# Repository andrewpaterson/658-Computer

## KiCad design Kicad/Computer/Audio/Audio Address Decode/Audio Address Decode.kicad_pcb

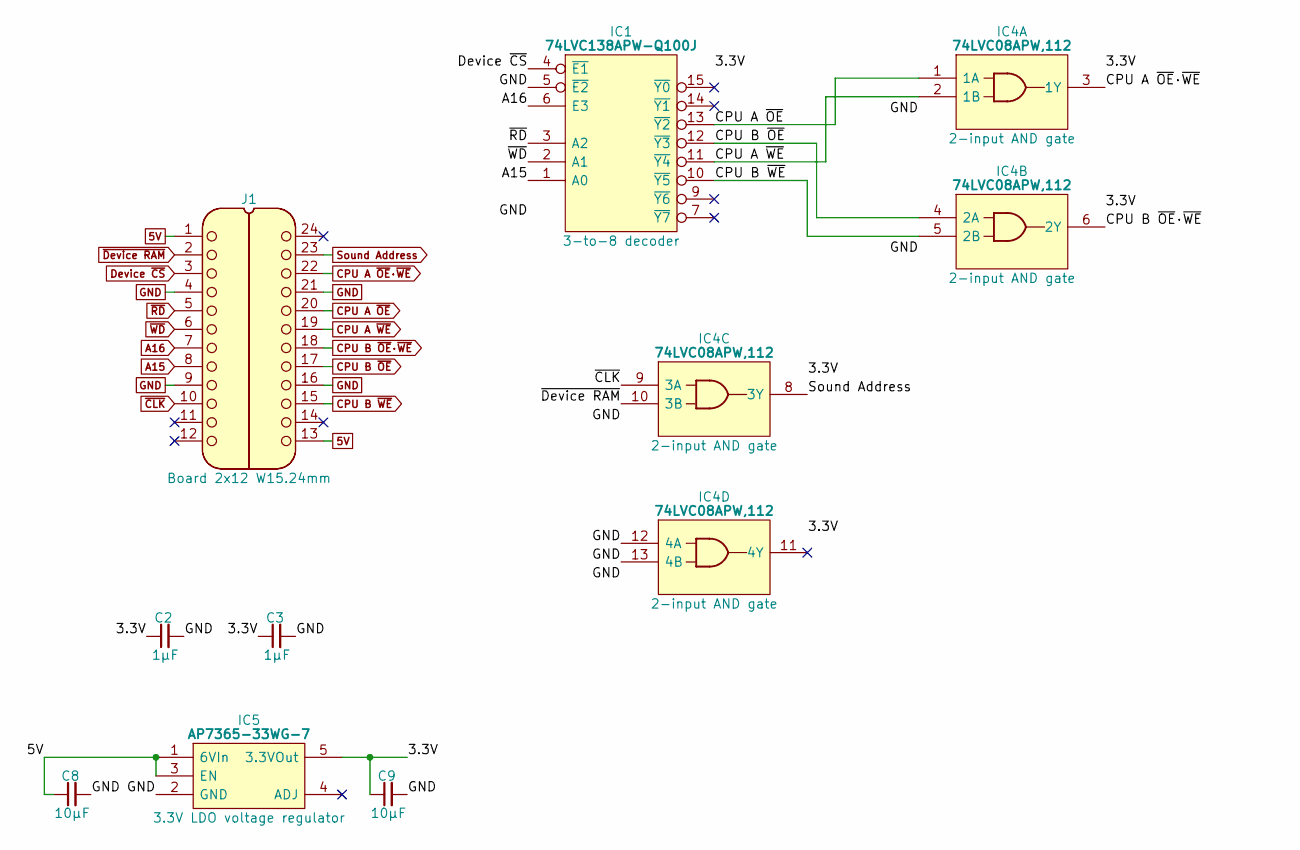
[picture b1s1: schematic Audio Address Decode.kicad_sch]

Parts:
C2, C3: 1μF; C_0805
C8, C9: 10µF; C_0805
IC1: 74LVC138APW-Q100J; SOP65P640X110-16N; Mouser Part Number 771-74LVC138APWQ100J
IC4: 74LVC08APW,112; SOP65P640X110-14N; Manufacturer_Part_Number 74LVC08APW,112; Mouser Part Number 771-74LVC08APW
IC5: AP7365-33WG-7; SOT95P285X130-5N; Manufacturer_Part_Number AP7365-33WG-7; Mouser Part Number 621-AP7365-33WG-7
J1: Board 2x12 W15.24mm; DIP-24_Board_W15.24mm

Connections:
5V: C8.1, IC5.1 (6VIn), IC5.3 (EN), J1.1, J1.13
/3.3V: C2.1, C3.1, C9.1, IC1.16 (3V), IC4.14 (3V), IC5.5 (3.3VOut)
A15: IC1.1 (A0), J1.8
A16: IC1.6 (E3), J1.7
CPU A ~OE: IC1.13 (~Y2), IC4.1 (1A), J1.20
CPU A ~OE·~WE: IC4.3 (1Y), J1.22
CPU A ~WE: IC1.11 (~Y4), IC4.2 (1B), J1.19
CPU B ~OE: IC1.12 (~Y3), IC4.4 (2A), J1.17
CPU B ~OE·~WE: IC4.6 (2Y), J1.18
CPU B ~WE: IC1.10 (~Y5), IC4.5 (2B), J1.15
Device ~CS: IC1.4 (~E1), J1.3
GND: C2.2, C3.2, C8.2, C9.2, IC1.5 (~E2), IC1.8 (GND), IC4.7 (GND), IC4.12 (4A), IC4.13 (4B), IC5.2 (GND), J1.4, J1.9, J1.16, J1.21
Sound Address: IC4.8 (3Y), J1.23
~CLK: IC4.9 (3A), J1.10
~Device RAM: IC4.10 (3B), J1.2
~RD: IC1.3 (A2), J1.5
~WD: IC1.2 (A1), J1.6

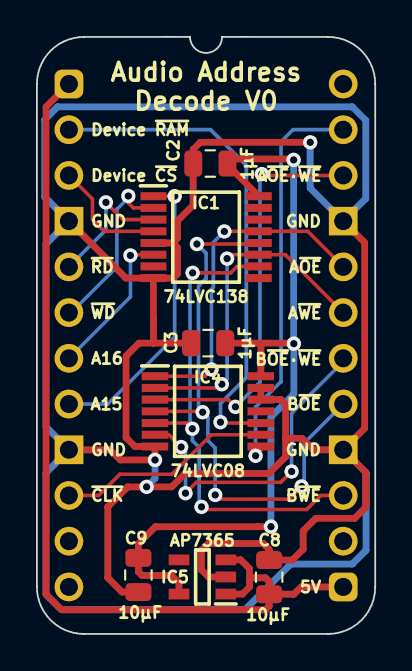
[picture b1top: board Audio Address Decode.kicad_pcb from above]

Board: 2 copper layers, 18.8 x 33.2 mm, 8 parts (0 on the bottom side), 17 nets.

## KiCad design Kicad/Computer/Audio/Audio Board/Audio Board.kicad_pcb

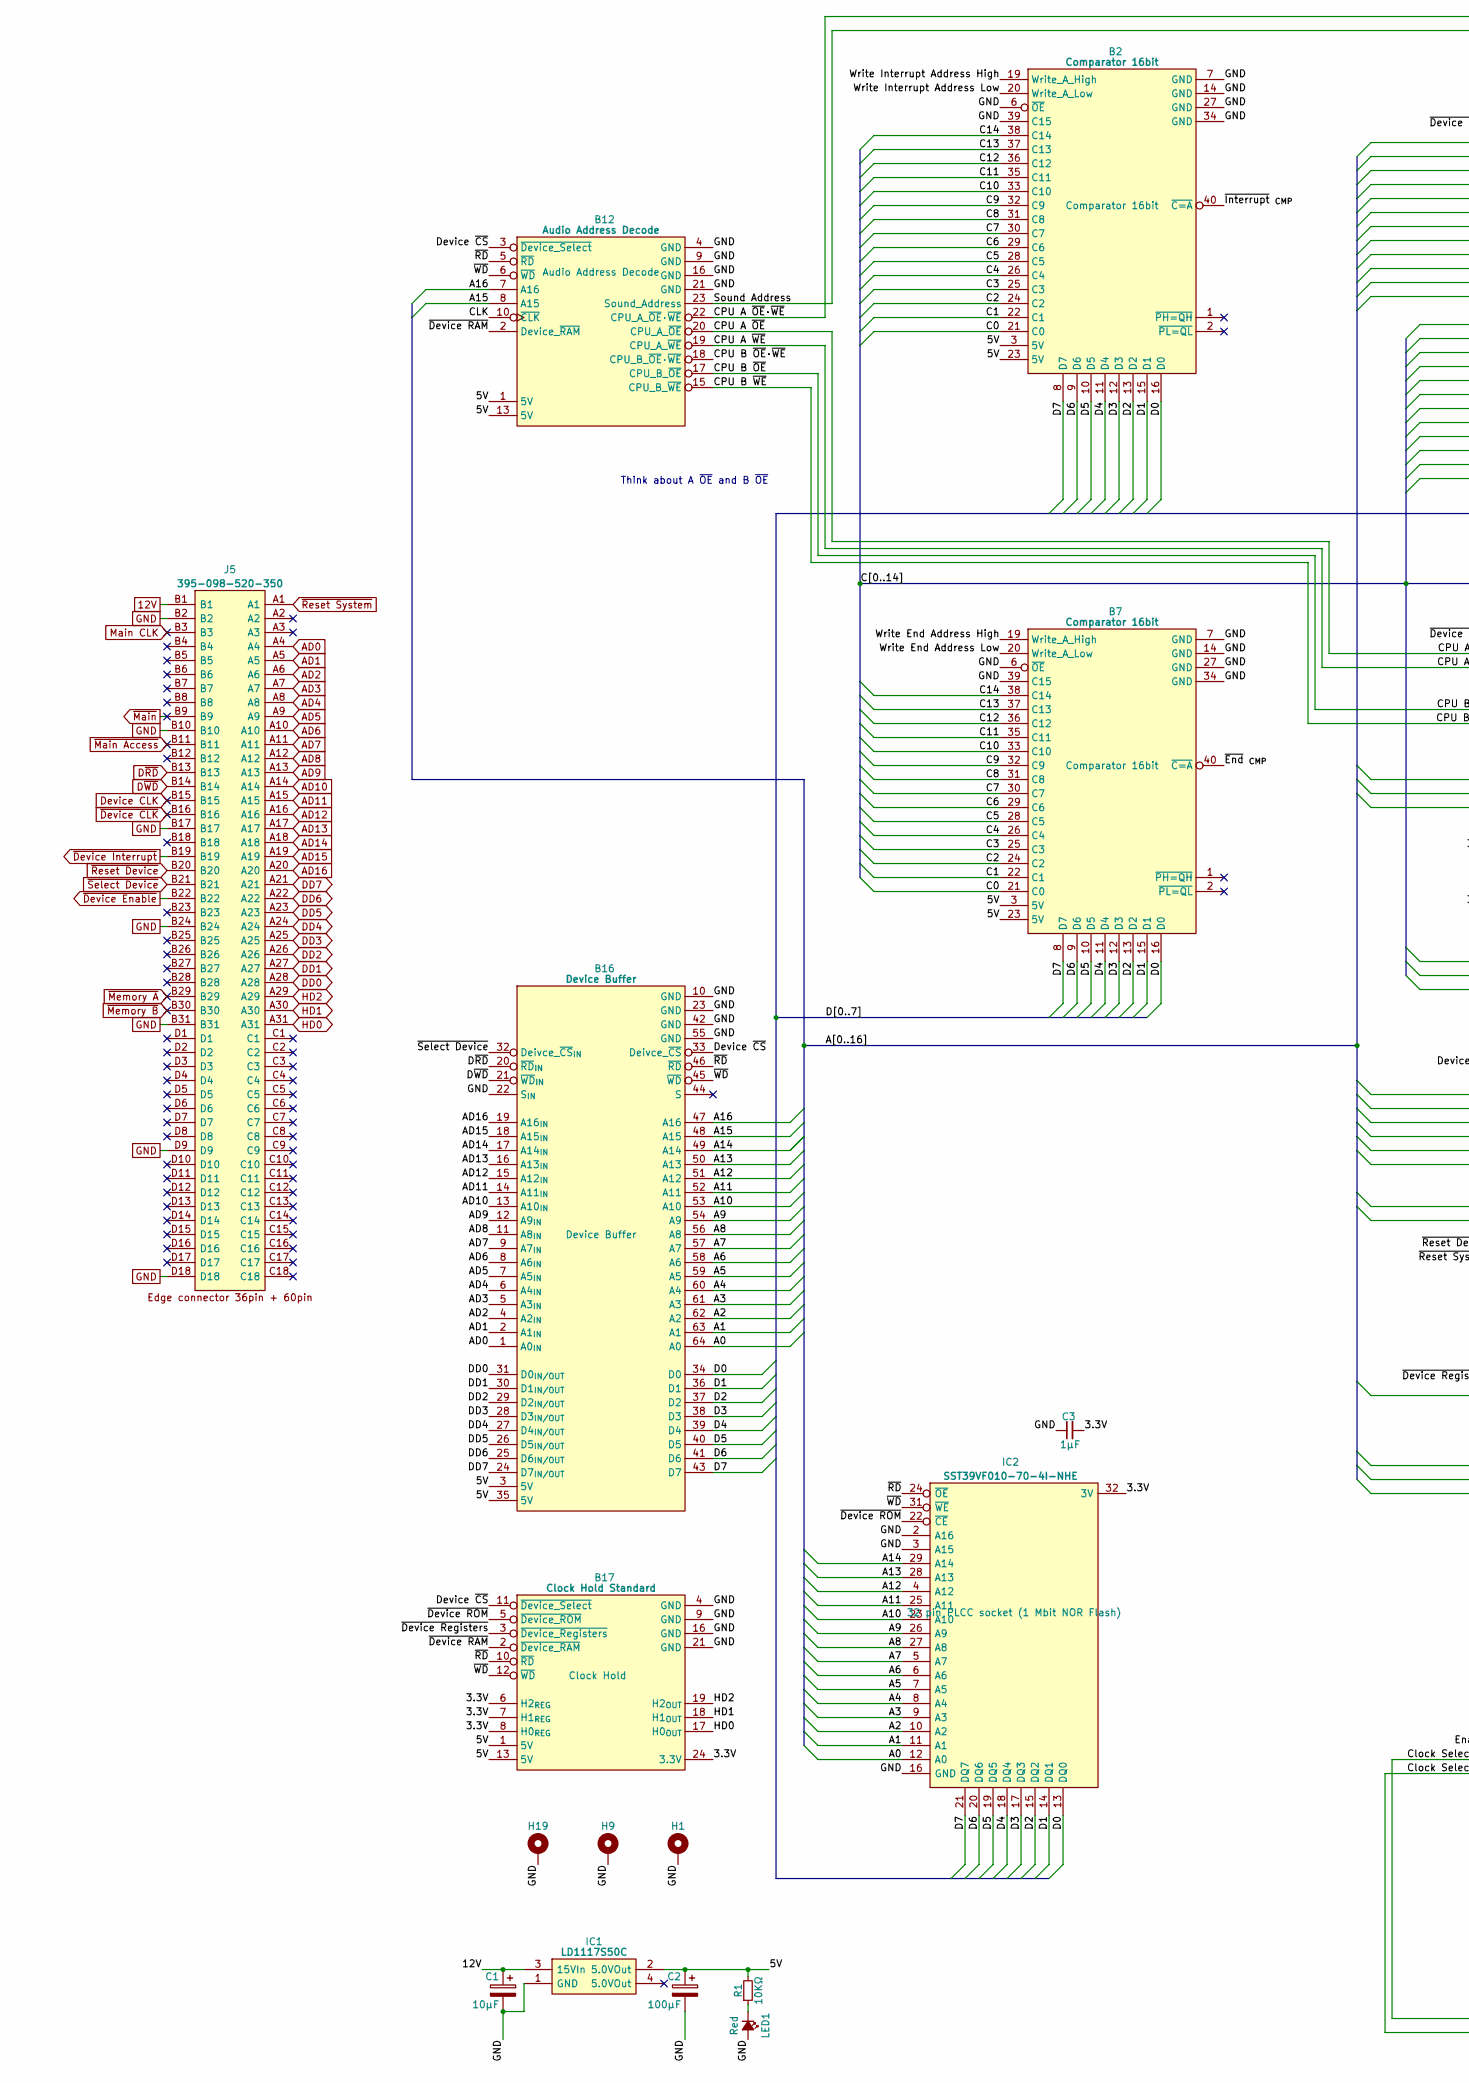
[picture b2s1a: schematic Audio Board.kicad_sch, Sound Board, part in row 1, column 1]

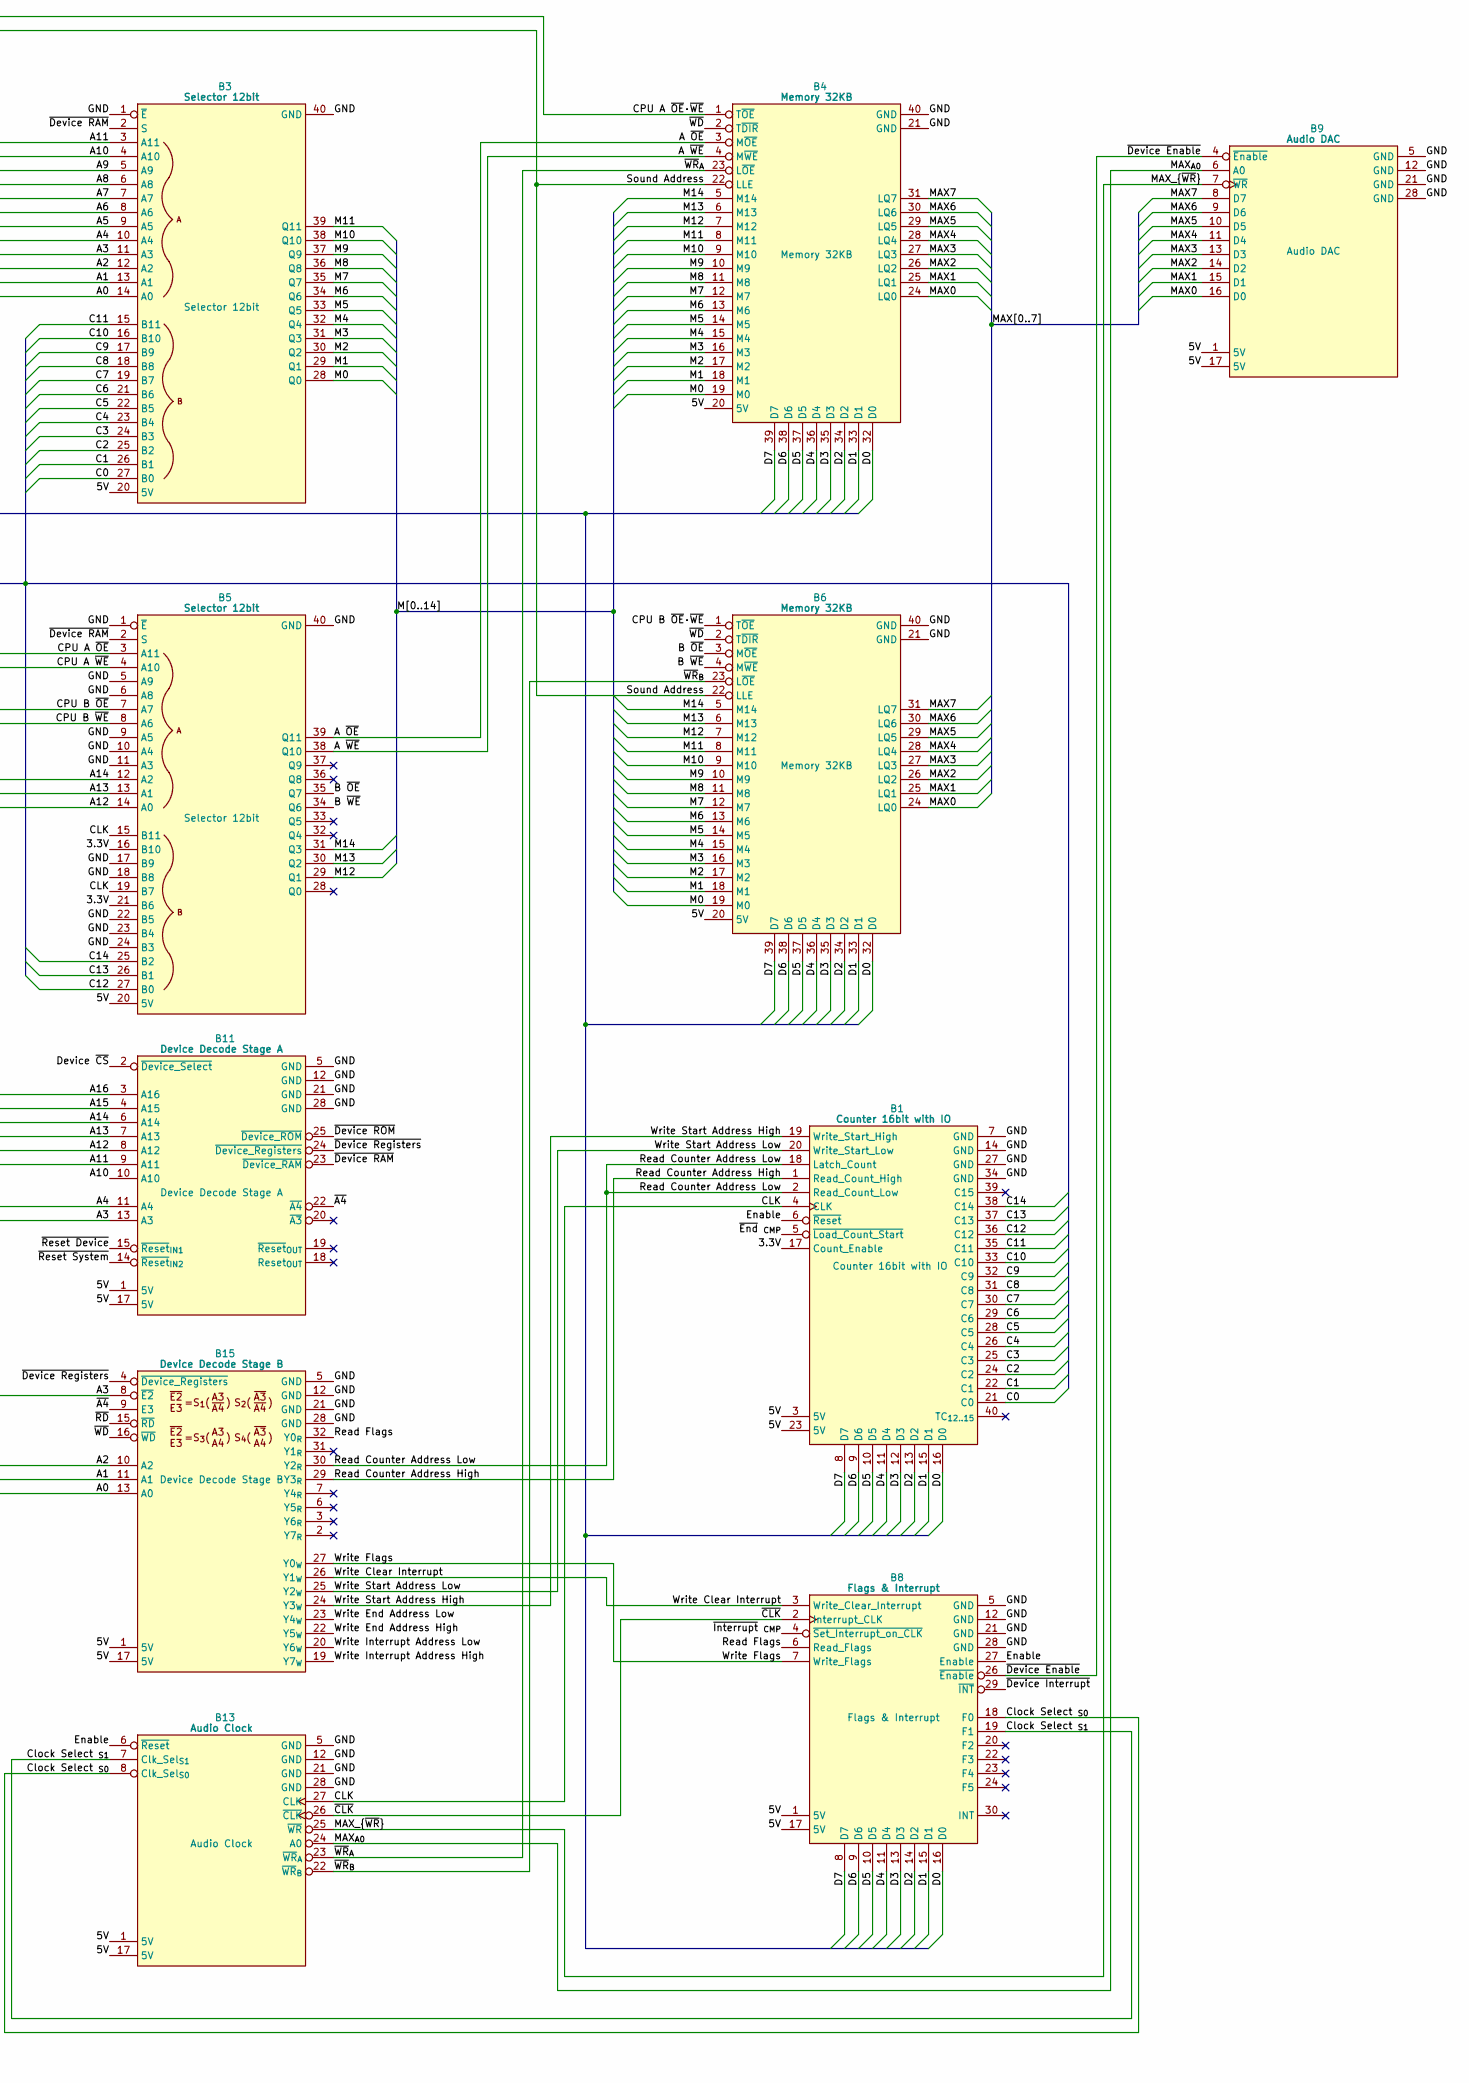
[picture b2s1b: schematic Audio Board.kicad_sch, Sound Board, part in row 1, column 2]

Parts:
B1: Counter 16bit with IO; HCP65_Counter_16bit_DIO
B2, B7: Comparator 16bit; HCP65_Comparator_16bit
B3, B5: Selector 12bit; HCP65_Selector_12bit
B4, B6: Memory 32KB; HCP65_Memory_32KB_With_Latch
B8: Flags & Interrupt; HCP65_Flags_Interrupt
B9: Audio DAC; HCP65_Audio_DAC
B11: Device Decode Stage A; HCP65_Device_Decode_Stage_A
B12: Audio Address Decode; HCP65_Audio_Address_Decode
B13: Audio Clock; HCP65_Audio_Clock
B15: Device Decode Stage B; HCP65_Device_Decode_Stage_B
B16: Device Buffer; HCP65_Device_Buffer
B17: Clock Hold Standard; HCP65_Clock_Hold_Standard
C1: 10μF; CP_Radial_D4.0mm_P2.00mm
C2: 100μF; CP_Radial_D4.0mm_P2.00mm
C3: 1μF; C_0805
H1, H9, H19: MountingHole_Pad; HCP65_MountingHole_M3_
IC1: LD1117S50C; LD1117S33C; Manufacturer_Part_Number LD1117S50C
IC2: SST39VF010-70-4I-NHE; 5408803224008; Manufacturer_Part_Number SST39VF010-70-4I-NHE
J5: 395-098-520-350; 98pin Edge Connector; Manufacturer_Part_Number 395-098-520-350; Mouser Part Number 587-395-098-520-350
LED1: Red; LED_D5.0mm
R1: 10KΩ; R_0805

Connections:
12V: C1.1, IC1.3 (15VIn), J5.B1
/3.3V: B1.17 (Count_Enable), B5.16 (B10), B5.21 (B6), B17.6 (H2_{REG}), B17.7 (H1_{REG}), B17.8 (H0_{REG}), B17.24 (3.3V), C3.2, IC2.32 (3V)
/5V: B1.3 (5V), B1.23 (5V), B2.3 (5V), B2.23 (5V), B3.20 (5V), B4.20 (5V), B5.20 (5V), B6.20 (5V), B7.3 (5V), B7.23 (5V), B8.1 (5V), B8.17 (5V), B9.1 (5V), B9.17 (5V), B11.1 (5V), B11.17 (5V), B12.1 (5V), B12.13 (5V), B13.1 (5V), B13.17 (5V), B15.1 (5V), B15.17 (5V), B16.3 (5V), B16.35 (5V), B17.1 (5V), B17.13 (5V), C2.1, IC1.2 (5.0VOut), R1.2
/A0: B3.14 (A0), B15.13 (A0), B16.64 (A0), IC2.12 (A0)
/A1: B3.13 (A1), B15.11 (A1), B16.63 (A1), IC2.11 (A1)
/A2: B3.12 (A2), B15.10 (A2), B16.62 (A2), IC2.10 (A2)
/A3: B3.11 (A3), B11.13 (A3), B15.8 (~E2), B16.61 (A3), IC2.9 (A3)
/A4: B3.10 (A4), B11.11 (A4), B16.60 (A4), IC2.8 (A4)
/A5: B3.9 (A5), B16.59 (A5), IC2.7 (A5)
/A6: B3.8 (A6), B16.58 (A6), IC2.6 (A6)
/A7: B3.7 (A7), B16.57 (A7), IC2.5 (A7)
/A8: B3.6 (A8), B16.56 (A8), IC2.27 (A8)
/A9: B3.5 (A9), B16.54 (A9), IC2.26 (A9)
/A10: B3.4 (A10), B11.10 (A10), B16.53 (A10), IC2.23 (A10)
/A11: B3.3 (A11), B11.9 (A11), B16.52 (A11), IC2.25 (A11)
/A12: B5.14 (A0), B11.8 (A12), B16.51 (A12), IC2.4 (A12)
/A13: B5.13 (A1), B11.7 (A13), B16.50 (A13), IC2.28 (A13)
/A14: B5.12 (A2), B11.6 (A14), B16.49 (A14), IC2.29 (A14)
/A15: B11.4 (A15), B12.8 (A15), B16.48 (A15)
/A16: B11.3 (A16), B12.7 (A16), B16.47 (A16)
/A ~OE: B4.3 (M~OE), B5.39 (Q11)
/A ~WE: B4.4 (M~WE), B5.38 (Q10)
/B ~OE: B5.35 (Q7), B6.3 (M~OE)
/B ~WE: B5.34 (Q6), B6.4 (M~WE)
/C0: B1.21 (C0), B2.21 (C0), B3.27 (B0), B7.21 (C0)
/C1: B1.22 (C1), B2.22 (C1), B3.26 (B1), B7.22 (C1)
/C2: B1.24 (C2), B2.24 (C2), B3.25 (B2), B7.24 (C2)
/C3: B1.25 (C3), B2.25 (C3), B3.24 (B3), B7.25 (C3)
/C4: B1.26 (C4), B2.26 (C4), B3.23 (B4), B7.26 (C4)
/C5: B1.28 (C5), B2.28 (C5), B3.22 (B5), B7.28 (C5)
/C6: B1.29 (C6), B2.29 (C6), B3.21 (B6), B7.29 (C6)
/C7: B1.30 (C7), B2.30 (C7), B3.19 (B7), B7.30 (C7)
/C8: B1.31 (C8), B2.31 (C8), B3.18 (B8), B7.31 (C8)
/C9: B1.32 (C9), B2.32 (C9), B3.17 (B9), B7.32 (C9)
/C10: B1.33 (C10), B2.33 (C10), B3.16 (B10), B7.33 (C10)
/C11: B1.35 (C11), B2.35 (C11), B3.15 (B11), B7.35 (C11)
/C12: B1.36 (C12), B2.36 (C12), B5.27 (B0), B7.36 (C12)
/C13: B1.37 (C13), B2.37 (C13), B5.26 (B1), B7.37 (C13)
/C14: B1.38 (C14), B2.38 (C14), B5.25 (B2), B7.38 (C14)
/CLK: B1.4 (CLK), B5.15 (B11), B5.19 (B7), B12.10 (~CLK), B13.27 (CLK)
/CPU A ~OE: B5.3 (A11), B12.20 (CPU_A_~OE)
/CPU A ~OE·~WE: B4.1 (T~OE), B12.22 (CPU_A_~OE·~WE)
/CPU A ~WE: B5.4 (A10), B12.19 (CPU_A_~WE)
/CPU B ~OE: B5.7 (A7), B12.17 (CPU_B_~OE)
/CPU B ~OE·~WE: B6.1 (T~OE), B12.18 (CPU_B_~OE·~WE)
/CPU B ~WE: B5.8 (A6), B12.15 (CPU_B_~WE)
/Clock Select _{S0}: B8.18 (F0), B13.8 (Clk_Sel_{S0})
/Clock Select _{S1}: B8.19 (F1), B13.7 (Clk_Sel_{S1})
/D0: B1.16 (D0), B2.16 (D0), B4.32 (D0), B6.32 (D0), B7.16 (D0), B8.16 (D0), B16.34 (D0), IC2.13 (DQ0)
/D1: B1.15 (D1), B2.15 (D1), B4.33 (D1), B6.33 (D1), B7.15 (D1), B8.15 (D1), B16.36 (D1), IC2.14 (DQ1)
/D2: B1.13 (D2), B2.13 (D2), B4.34 (D2), B6.34 (D2), B7.13 (D2), B8.14 (D2), B16.37 (D2), IC2.15 (DQ2)
/D3: B1.12 (D3), B2.12 (D3), B4.35 (D3), B6.35 (D3), B7.12 (D3), B8.13 (D3), B16.38 (D3), IC2.17 (DQ3)
/D4: B1.11 (D4), B2.11 (D4), B4.36 (D4), B6.36 (D4), B7.11 (D4), B8.11 (D4), B16.39 (D4), IC2.18 (DQ4)
/D5: B1.10 (D5), B2.10 (D5), B4.37 (D5), B6.37 (D5), B7.10 (D5), B8.10 (D5), B16.40 (D5), IC2.19 (DQ5)
/D6: B1.9 (D6), B2.9 (D6), B4.38 (D6), B6.38 (D6), B7.9 (D6), B8.9 (D6), B16.41 (D6), IC2.20 (DQ6)
/D7: B1.8 (D7), B2.8 (D7), B4.39 (D7), B6.39 (D7), B7.8 (D7), B8.8 (D7), B16.43 (D7), IC2.21 (DQ7)
/Device ~CS: B11.2 (~Device_Select), B12.3 (~Device_Select), B16.33 (Deivce_~CS), B17.11 (~Device_Select)
/Enable: B1.6 (~Reset), B8.27 (Enable), B13.6 (~Reset)
/M0: B3.28 (Q0), B4.19 (M0), B6.19 (M0)
/M1: B3.29 (Q1), B4.18 (M1), B6.18 (M1)
/M2: B3.30 (Q2), B4.17 (M2), B6.17 (M2)
/M3: B3.31 (Q3), B4.16 (M3), B6.16 (M3)
/M4: B3.32 (Q4), B4.15 (M4), B6.15 (M4)
/M5: B3.33 (Q5), B4.14 (M5), B6.14 (M5)
/M6: B3.34 (Q6), B4.13 (M6), B6.13 (M6)
/M7: B3.35 (Q7), B4.12 (M7), B6.12 (M7)
/M8: B3.36 (Q8), B4.11 (M8), B6.11 (M8)
/M9: B3.37 (Q9), B4.10 (M9), B6.10 (M9)
/M10: B3.38 (Q10), B4.9 (M10), B6.9 (M10)
/M11: B3.39 (Q11), B4.8 (M11), B6.8 (M11)
/M12: B4.7 (M12), B5.29 (Q1), B6.7 (M12)
/M13: B4.6 (M13), B5.30 (Q2), B6.6 (M13)
/M14: B4.5 (M14), B5.31 (Q3), B6.5 (M14)
/MAX0: B4.24 (LQ0), B6.24 (LQ0), B9.16 (D0)
/MAX1: B4.25 (LQ1), B6.25 (LQ1), B9.15 (D1)
/MAX2: B4.26 (LQ2), B6.26 (LQ2), B9.14 (D2)
/MAX3: B4.27 (LQ3), B6.27 (LQ3), B9.13 (D3)
/MAX4: B4.28 (LQ4), B6.28 (LQ4), B9.11 (D4)
/MAX5: B4.29 (LQ5), B6.29 (LQ5), B9.10 (D5)
/MAX6: B4.30 (LQ6), B6.30 (LQ6), B9.9 (D6)
/MAX7: B4.31 (LQ7), B6.31 (LQ7), B9.8 (D7)
/MAX_{A0}: B9.6 (A0), B13.24 (A0)
/MAX_{~WR}: B9.7 (~WR), B13.25 (~WR)
/Read Counter Address High: B1.1 (Read_Count_High), B15.29 (Y3_{R})
/Read Counter Address Low: B1.2 (Read_Count_Low), B1.18 (Latch_Count), B15.30 (Y2_{R})
/Read Flags: B8.6 (Read_Flags), B15.32 (Y0_{R})
/Sound Address: B4.22 (LLE), B6.22 (LLE), B12.23 (Sound_Address)
/Write Clear Interrupt: B8.3 (Write_Clear_Interrupt), B15.26 (Y1_{W})
/Write End Address High: B7.19 (Write_A_High), B15.22 (Y5_{W})
/Write End Address Low: B7.20 (Write_A_Low), B15.23 (Y4_{W})
/Write Flags: B8.7 (Write_Flags), B15.27 (Y0_{W})
/Write Interrupt Address High: B2.19 (Write_A_High), B15.19 (Y7_{W})
/Write Interrupt Address Low: B2.20 (Write_A_Low), B15.20 (Y6_{W})
/Write Start Address High: B1.19 (Write_Start_High), B15.24 (Y3_{W})
/Write Start Address Low: B1.20 (Write_Start_Low), B15.25 (Y2_{W})
/~A4: B11.22 (~A4), B15.9 (E3)
/~CLK: B8.2 (Interrupt_CLK), B13.26 (~CLK)
/~Device RAM: B3.2 (S), B5.2 (S), B11.23 (~Device_RAM), B12.2 (Device_~RAM), B17.2 (~Device_RAM)
/~Device ROM: B11.25 (~Device_ROM), B17.5 (~Device_ROM), IC2.22 (~CE)
/~Device Registers: B11.24 (~Device_Registers), B15.4 (~Device_Registers), B17.3 (~Device_Registers)
/~End _{CMP}: B1.5 (~Load_Count_Start), B7.40 (~C=A)
/~Interrupt _{CMP}: B2.40 (~C=A), B8.4 (~Set_Interrupt_on_CLK)
/~RD: B12.5 (~RD), B15.15 (~RD), B16.46 (~RD), B17.10 (~RD), IC2.24 (~OE)
/~WD: B4.2 (T~DIR), B6.2 (T~DIR), B12.6 (~WD), B15.16 (~WD), B16.45 (~WD), B17.12 (~WD), IC2.31 (~WE)
/~WR_{A}: B4.23 (L~OE), B13.23 (~WR_{A})
/~WR_{B}: B6.23 (L~OE), B13.22 (~WR_{B})
AD0: B16.1 (A0_{IN}), J5.A4
AD1: B16.2 (A1_{IN}), J5.A5
AD2: B16.4 (A2_{IN}), J5.A6
AD3: B16.5 (A3_{IN}), J5.A7
AD4: B16.6 (A4_{IN}), J5.A8
AD5: B16.7 (A5_{IN}), J5.A9
AD6: B16.8 (A6_{IN}), J5.A10
AD7: B16.9 (A7_{IN}), J5.A11
AD8: B16.11 (A8_{IN}), J5.A12
AD9: B16.12 (A9_{IN}), J5.A13
AD10: B16.13 (A10_{IN}), J5.A14
AD11: B16.14 (A11_{IN}), J5.A15
AD12: B16.15 (A12_{IN}), J5.A16
AD13: B16.16 (A13_{IN}), J5.A17
AD14: B16.17 (A14_{IN}), J5.A18
AD15: B16.18 (A15_{IN}), J5.A19
AD16: B16.19 (A16_{IN}), J5.A20
DD0: B16.31 (D0_{IN/OUT}), J5.A28
DD1: B16.30 (D1_{IN/OUT}), J5.A27
DD2: B16.29 (D2_{IN/OUT}), J5.A26
DD3: B16.28 (D3_{IN/OUT}), J5.A25
DD4: B16.27 (D4_{IN/OUT}), J5.A24
DD5: B16.26 (D5_{IN/OUT}), J5.A23
DD6: B16.25 (D6_{IN/OUT}), J5.A22
DD7: B16.24 (D7_{IN/OUT}), J5.A21
Device CLK: J5.B15
D~RD: B16.20 (~RD_{IN}), J5.B13
D~WD: B16.21 (~WD_{IN}), J5.B14
GND: B1.7 (GND), B1.14 (GND), B1.27 (GND), B1.34 (GND), B2.6 (~OE), B2.7 (GND), B2.14 (GND), B2.27 (GND), B2.34 (GND), B2.39 (C15), B3.1 (~E), B3.40 (GND), B4.21 (GND), B4.40 (GND), B5.1 (~E), B5.5 (A9), B5.6 (A8), B5.9 (A5), B5.10 (A4), B5.11 (A3), B5.17 (B9), B5.18 (B8), B5.22 (B5), B5.23 (B4), B5.24 (B3), B5.40 (GND), B6.21 (GND), B6.40 (GND), B7.6 (~OE), B7.7 (GND), B7.14 (GND), B7.27 (GND), B7.34 (GND), B7.39 (C15), B8.5 (GND), B8.12 (GND), B8.21 (GND), B8.28 (GND), B9.5 (GND), B9.12 (GND), B9.21 (GND), B9.28 (GND), B11.5 (GND), B11.12 (GND), B11.21 (GND), B11.28 (GND), B12.4 (GND), B12.9 (GND), B12.16 (GND), B12.21 (GND), B13.5 (GND), B13.12 (GND), B13.21 (GND), B13.28 (GND), B15.5 (GND), B15.12 (GND), B15.21 (GND), B15.28 (GND), B16.10 (GND), B16.22 (S_{IN}), B16.23 (GND), B16.42 (GND), B16.55 (GND), B17.4 (GND), B17.9 (GND), B17.16 (GND), B17.21 (GND), C1.2, C2.2, C3.1, H1.1 (GND), H9.1 (GND), H19.1 (GND), IC1.1 (GND), IC2.2 (A16), IC2.3 (A15), IC2.16 (GND), J5.B2, J5.B10, J5.B17, J5.B24, J5.B31, J5.D9, J5.D18, LED1.2 (A)
HD0: B17.17 (H0_{OUT}), J5.A31
HD1: B17.18 (H1_{OUT}), J5.A30
HD2: B17.19 (H2_{OUT}), J5.A29
Main CLK: J5.B3
unnamed: LED1.1 (K), R1.1
~Device CLK: J5.B16
~Device Enable: B8.26 (~Enable), B9.4 (~Enable), J5.B22
~Device Interrupt: B8.29 (~INT), J5.B19
~Main Access: J5.B11
~Main: J5.B9
~Memory A: J5.B29
~Memory B: J5.B30
~Reset Device: B11.15 (~Reset_{IN1}), J5.B20
~Reset System: B11.14 (~Reset_{IN2}), J5.A1
~Select Device: B16.32 (Deivce_~CS_{IN}), J5.B21

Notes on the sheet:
Think about A ~{OE} and B ~{OE}

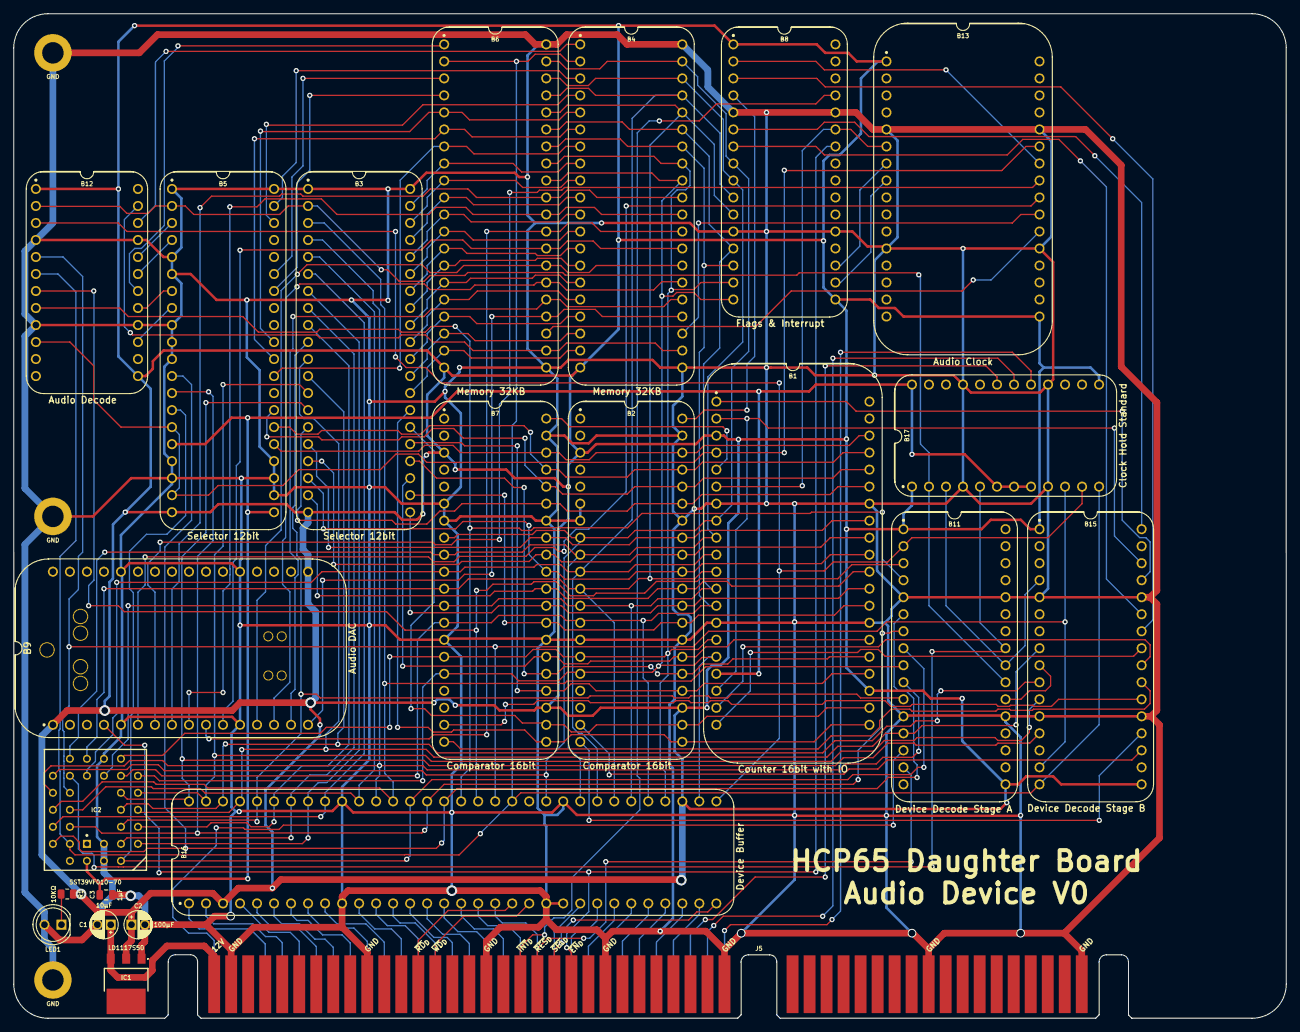
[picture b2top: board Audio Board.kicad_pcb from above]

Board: 2 copper layers, 190.0 x 150.0 mm, 26 parts (0 on the bottom side), 143 nets.

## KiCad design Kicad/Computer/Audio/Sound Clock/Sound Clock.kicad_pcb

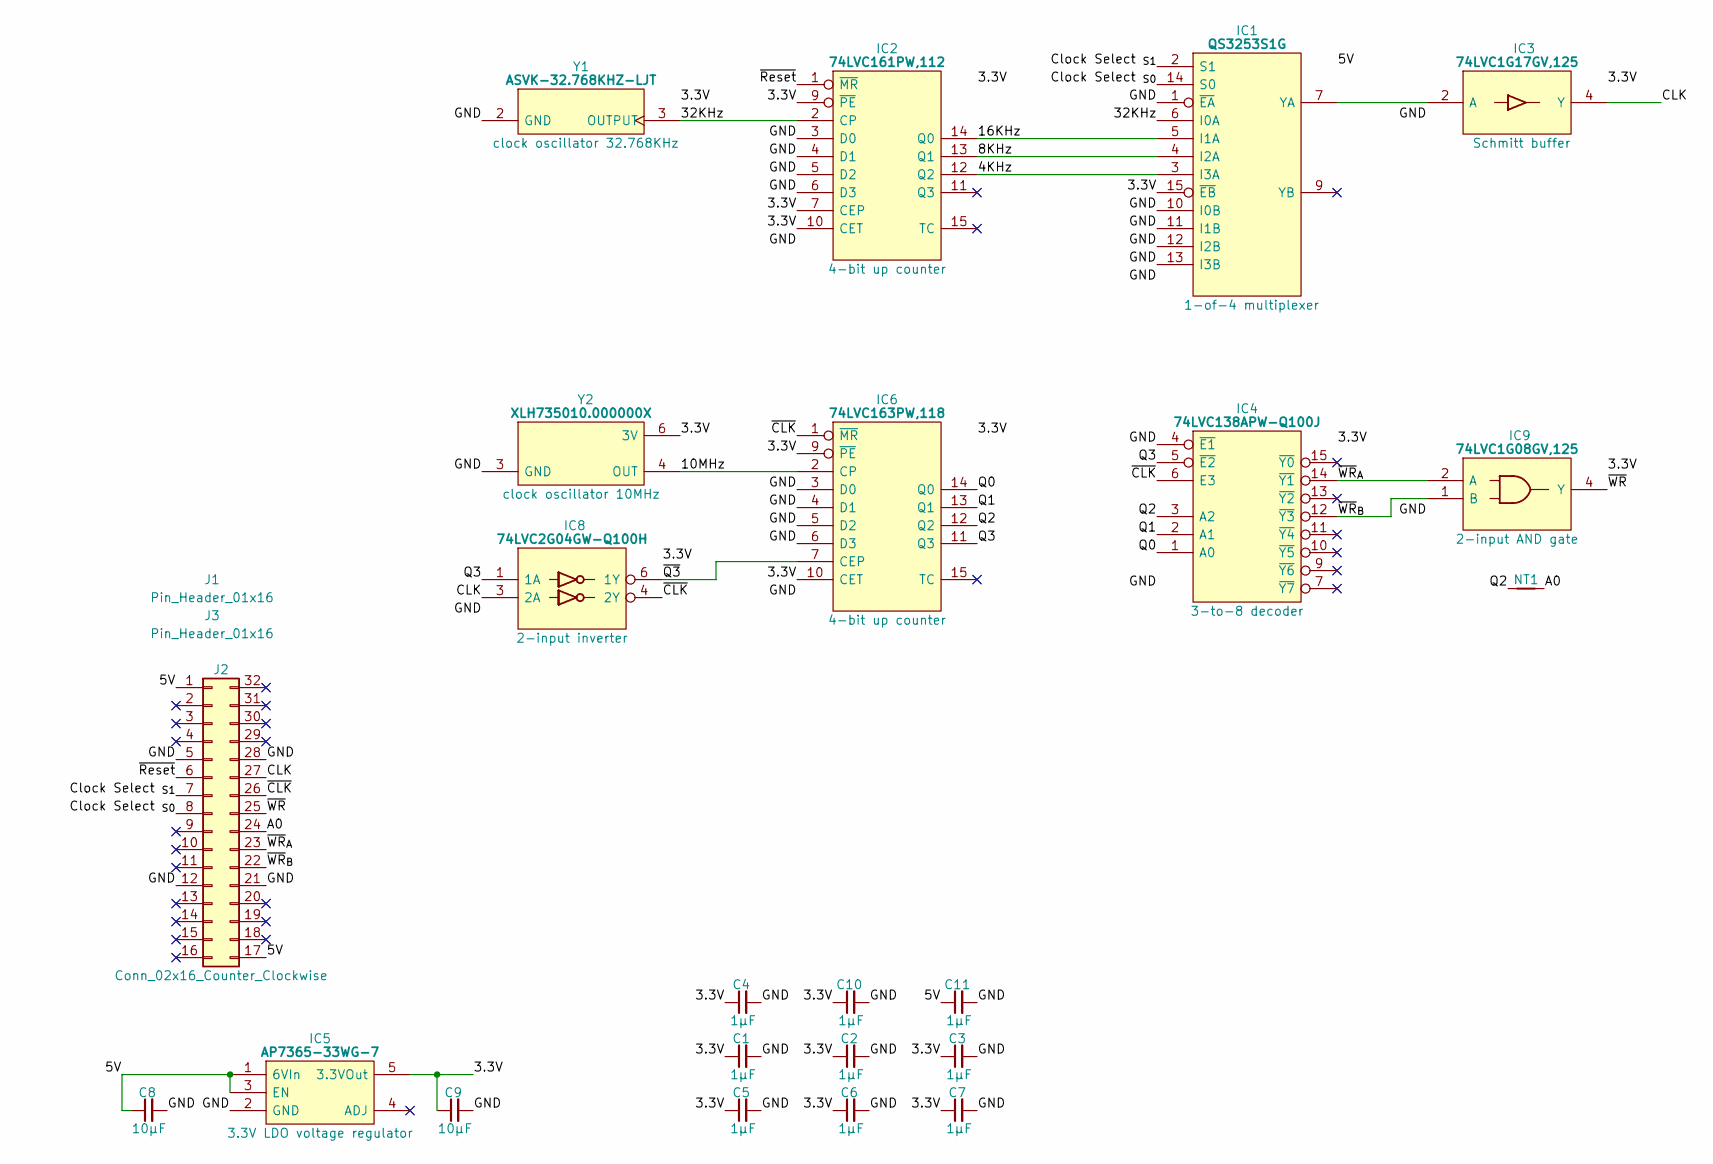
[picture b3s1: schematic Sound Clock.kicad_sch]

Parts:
C1, C2, C3, C4, C5, C6, C7, C10, C11: 1μF; C_0805
C8, C9: 10µF; C_0805
IC1: QS3253S1G; SOIC127P602X173-16N; Manufacturer_Part_Number QS3253S1G
IC2: 74LVC161PW,112; SOP65P640X110-16N; Mouser Part Number 771-LVC161PW112
IC3: 74LVC1G17GV,125; SOT95P275X110-5N; Manufacturer_Part_Number 74LVC1G17GV,125; Mouser Part Number 771-LVC1G17GV125
IC4: 74LVC138APW-Q100J; SOP65P640X110-16N; Mouser Part Number 771-74LVC138APWQ100J
IC5: AP7365-33WG-7; SOT95P285X130-5N; Manufacturer_Part_Number AP7365-33WG-7; Mouser Part Number 621-AP7365-33WG-7
IC6: 74LVC163PW,118; SOP65P640X110-16N; Mouser Part Number 771-74LVC163PW-T
IC8: 74LVC2G04GW-Q100H; SOP65P210X110-6N; Manufacturer_Part_Number 74LVC2G04GW-Q100H; Mouser Part Number 771-74LVC2G04GWQ100H
IC9: 74LVC1G08GV,125; SOT95P275X110-5N; Manufacturer_Part_Number 74LVC1G08GV,125; Mouser Part Number 771-74LVC1G08GV
J1, J3: Pin_Header_01x16; PinHeader_1x16_P2.54mm_Vertical
J2: Conn_02x16_Counter_Clockwise; DIP-32_Board_W22.86mm
NT1: NetTie; NetTie-2_SMD_Pad0.5mm
Y1: ASVK-32.768KHZ-LJT; ASVK32768KHZLJT; Manufacturer_Part_Number ASVK-32.768KHZ-LJT; Mouser Part Number 815-ASVK-32.768KLJT
Y2: XLH735010.000000X; XLH735100000000I; Manufacturer_Part_Number XLH735010.000000X; Mouser Part Number 972-XLH735010000000X

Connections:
/3.3V: C1.1, C2.1, C3.1, C4.1, C5.1, C6.1, C7.1, C9.1, C10.1, IC1.15 (~EB), IC2.7 (CEP), IC2.9 (~PE), IC2.10 (CET), IC2.16 (3V), IC3.5 (3V), IC4.16 (3V), IC5.5 (3.3VOut), IC6.9 (~PE), IC6.10 (CET), IC6.16 (3V), IC8.5 (3V), IC9.5 (3V), Y1.4 (3V), Y2.6 (3V)
/4KHz: IC1.3 (I3A), IC2.12 (Q2)
/5V: C8.1, C11.1, IC1.16 (5V), IC5.1 (6VIn), IC5.3 (EN), J2.1, J2.17
/8KHz: IC1.4 (I2A), IC2.13 (Q1)
/10MHz: IC6.2 (CP), Y2.4 (OUT)
/16KHz: IC1.5 (I1A), IC2.14 (Q0)
/32KHz: IC1.6 (I0A), IC2.2 (CP), Y1.3 (OUTPUT)
/A0: J2.24, NT1.2
/CLK: IC3.4 (Y), IC8.3 (2A), J2.27
/Clock Select _{S0}: IC1.14 (S0), J2.8
/Clock Select _{S1}: IC1.2 (S1), J2.7
/GND: C1.2, C2.2, C3.2, C4.2, C5.2, C6.2, C7.2, C8.2, C9.2, C10.2, C11.2, IC1.1 (~EA), IC1.8 (GND), IC1.10 (I0B), IC1.11 (I1B), IC1.12 (I2B), IC1.13 (I3B), IC2.3 (D0), IC2.4 (D1), IC2.5 (D2), IC2.6 (D3), IC2.8 (GND), IC3.3 (GND), IC4.4 (~E1), IC4.8 (GND), IC5.2 (GND), IC6.3 (D0), IC6.4 (D1), IC6.5 (D2), IC6.6 (D3), IC6.8 (GND), IC8.2 (GND), IC9.3 (GND), J2.5, J2.12, J2.21, J2.28, Y1.2 (GND), Y2.3 (GND)
/Q0: IC4.1 (A0), IC6.14 (Q0)
/Q1: IC4.2 (A1), IC6.13 (Q1)
/Q2: IC4.3 (A2), IC6.12 (Q2), NT1.1
/Q3: IC4.5 (~E2), IC6.11 (Q3), IC8.1 (1A)
/~CLK: IC4.6 (E3), IC6.1 (~MR), IC8.4 (2Y), J2.26
/~Q3: IC6.7 (CEP), IC8.6 (1Y)
/~Reset: IC2.1 (~MR), J2.6
/~WR: IC9.4 (Y), J2.25
/~WR_{A}: IC4.14 (~Y1), IC9.2 (A), J2.23
/~WR_{B}: IC4.12 (~Y3), IC9.1 (B), J2.22
unnamed: IC1.7 (YA), IC3.2 (A)

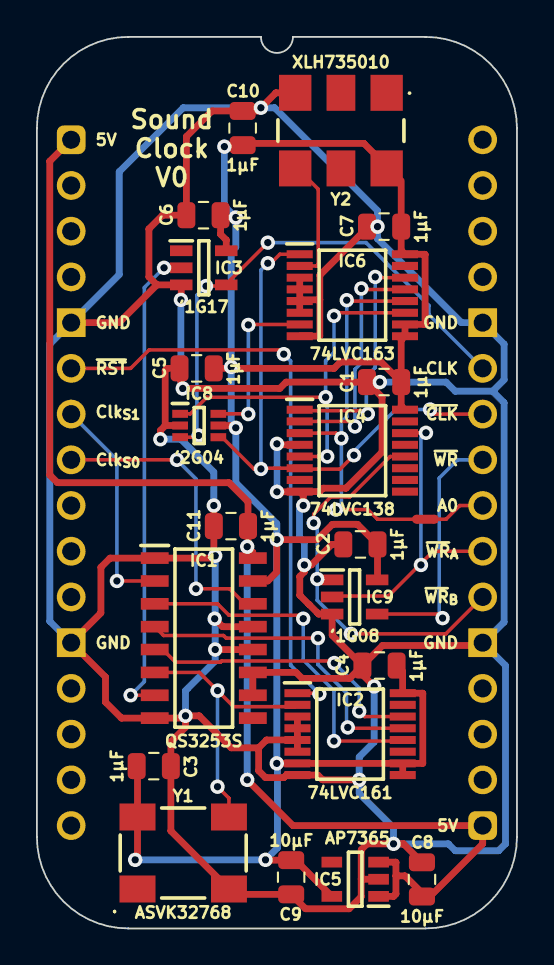
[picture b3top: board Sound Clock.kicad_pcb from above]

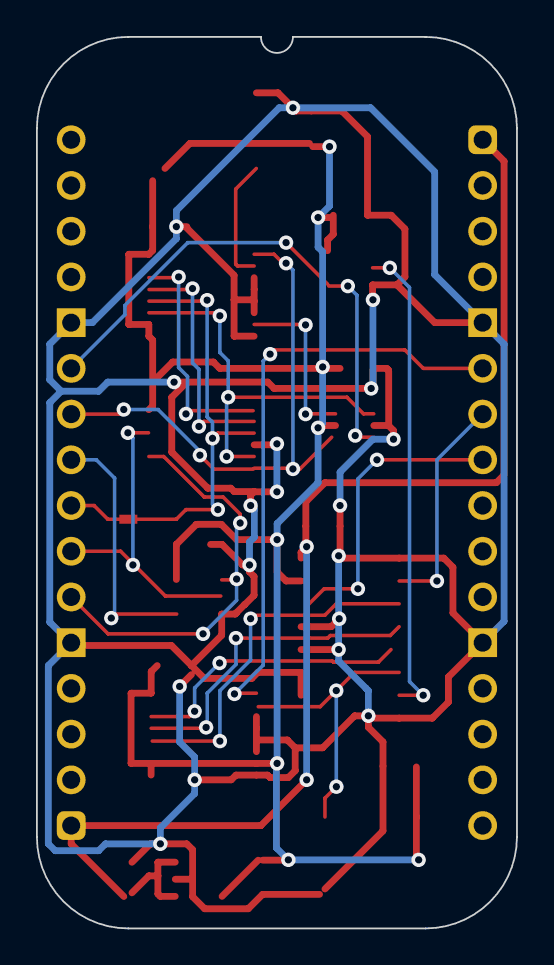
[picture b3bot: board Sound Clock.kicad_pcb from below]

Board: 2 copper layers, 26.7 x 49.5 mm, 25 parts (2 on the bottom side), 23 nets.

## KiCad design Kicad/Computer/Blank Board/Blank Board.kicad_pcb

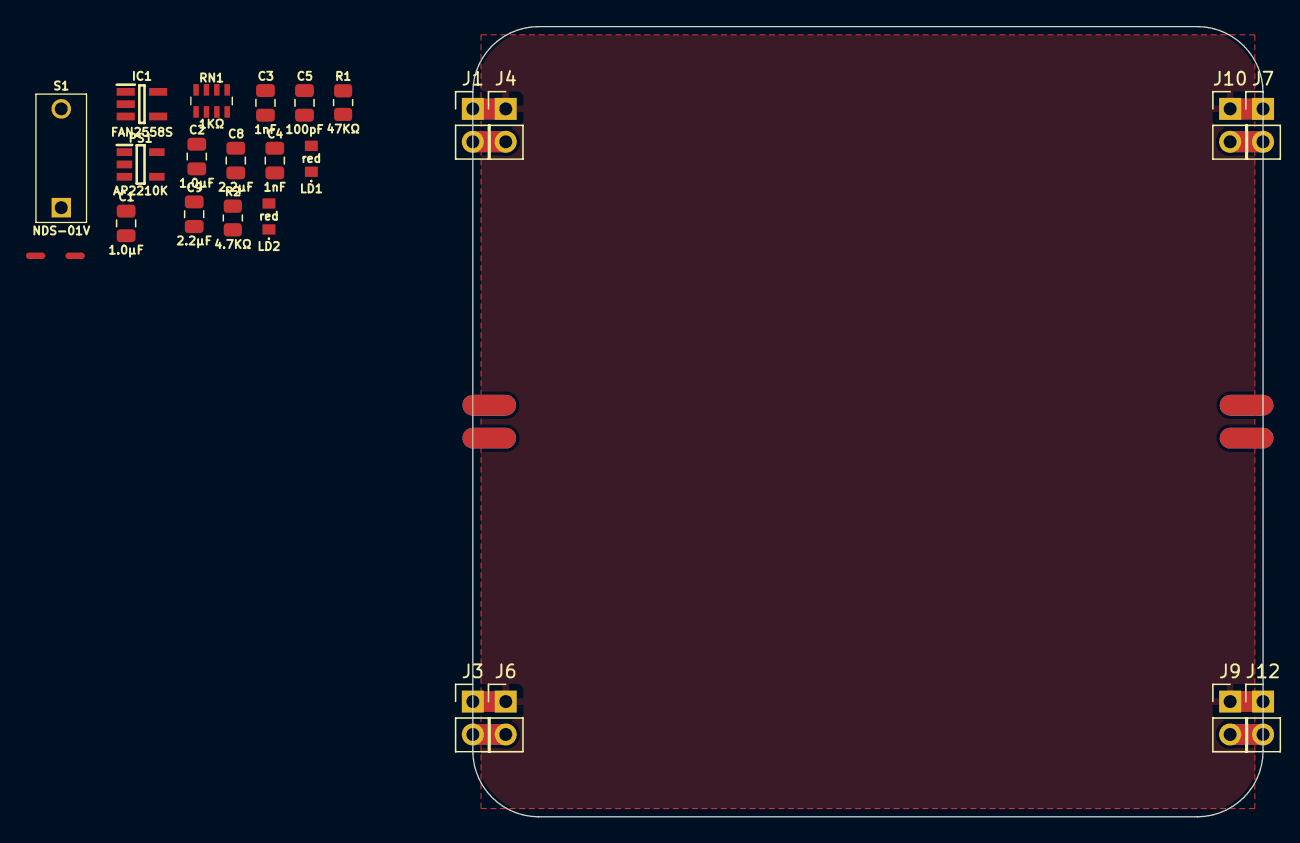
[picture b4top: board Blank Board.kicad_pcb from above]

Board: 2 copper layers, 61.0 x 61.0 mm, 25 parts (0 on the bottom side), 11 nets.

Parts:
C1, C2, C3, C4, C5, C8, C9: C_0805
IC1: FAN2558S38X; SOT95P270X145-5N
J1, J3, J4, J6, J7, J9, J10, J12: Conn_01x02_Male; PinHeader_1x02_P2.54mm_Vertical
LD1, LD2: 150224SS73100; 150224SS73100A
NT1, NT2: NetTie_2; NetTie-2_SMD_Pad0.5mm
PS1: AP2210K-5.0TRG1; SOT95P282X130-5N
R1, R2: R_0805
RN1: CAY16-102J4LF; CAY16-J4
S1: NDS-01V; NDS01V

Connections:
/3.8V: C9.1, IC1.5 (VOUT)
/5V: C3.1, C4.1, C8.1, NT1.1, PS1.5 (VOUT), R2.2
/GND: C1.2, C2.2, C3.2, C4.2, C5.2, C8.2, C9.2, IC1.2 (GND), J1.1, J3.1, J4.1, J6.1, J7.1, J9.1, J10.1, J12.1, PS1.2 (GND), RN1.1 (R1), RN1.4 (R4), S1.2 (NO)
/LED Enable: R2.1, S1.1 (COM)
/Power LED: LD1.2, NT1.2
/Reset LED: LD2.2, NT2.2
/Source 5V: C1.1, C2.1, IC1.1 (VIN), IC1.3 (EN), J3.2, J6.2, PS1.1 (VIN), PS1.3 (EN), R1.2
/~Power Error: IC1.4 (PG), R1.1
unnamed: C5.1, PS1.4 (BYP)
unnamed: LD1.1, RN1.8 (R1)
unnamed: LD2.1, RN1.5 (R4)
